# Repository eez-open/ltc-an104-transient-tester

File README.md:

LTC [AN104](http://www.linear.com/docs/29876) Closed loop load transient tester Eagle, Gebgers and BOM. It could be used for testing various LDOs, power supplies, etc.
Two PCB variants are available: 

* with power supply (ac-powered) that can be housed e.g. into Hammond diecast aluminium enclosure HM-1590U 
* without power supply (dc-powered) using two external 15 VDC sources connected with 2.1/5.5 mm DC plugs.

**Please note that max. allowed D.U.T voltage is determined with switching transistor SOA.**

**********************

Repository: www.github.com/eez-open
Web site: www.envox.hr/eez

**********************

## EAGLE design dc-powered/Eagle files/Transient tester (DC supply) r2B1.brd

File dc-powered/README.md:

LTC [AN104](http://www.linear.com/docs/29876) Closed loop load transient tester with external 2 x 15 VDC supply

**Please note that max. allowed D.U.T voltage is determined with switching transistor SOA.**

**********************

Repository: www.github.com/eez-open
Web site: www.envox.hr/eez

**********************

*EEZ 2-layer (+tKeepout +_tNames) *job script is used for generating Gerber files. Use [gerbv](http://gerbv.geda-project.org/), a free/open source Gerber viewer to inspect generated files.

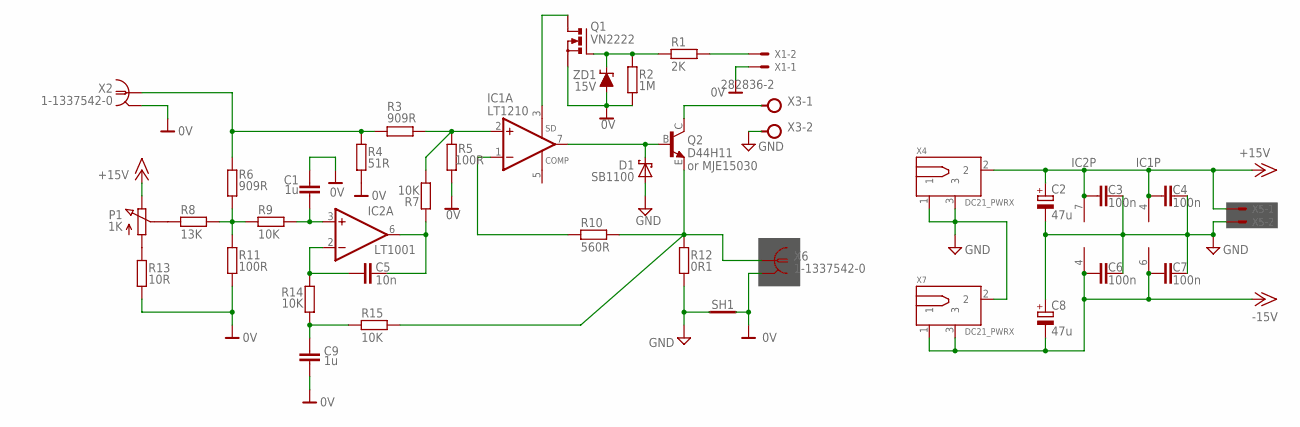
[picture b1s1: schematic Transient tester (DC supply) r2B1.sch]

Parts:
C1, C9: 1u; C050-075X075
C2, C8: 47u; ECAP2.5/7
C3, C4, C6, C7: 100n; C050-025X075
C5: 10n; C050-025X075
D1: SB1100; DO34/10
IC1: LT1210; TO220-7
IC2: LT1001; DIL08D
P1: 1K; BOURNS_POT91
Q1: VN2222; TO92-SGD
Q2: D44H11; TO220BV
R1: 2K; 0204/5
R2: 1M; 0204/5
R3, R6: 909R; 0207/10
R4: 51R; 0204/5
R5, R11: 100R; 0204/5
R7, R9, R14, R15: 10K; 0204/5
R8: 13K; 0204/5
R10: 560R; 0204/5
R12: 0R1; OAR1+2512
R13: 10R; 0204/5
SH1: SHORTH; SHORT_2
X1: 22-23-2021
X2, X6: 1-1337542-0; AMP_227161
X3: 282836-2; TBLOCK5.0_2
X4, X7: DC21_PWRX; DC-21MM
X5: 22-23-2021; MPN 22-23-2021
ZD1: 15V; DO34-ZD

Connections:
0V: C1.1, C9.2, Q1.S, R2.1, R4.1, R5.2, R11.1, R13.1, SH1.2 (GND_B), X1.1, X2.2 (GND), X6.2 (GND), ZD1.A
+15V: C2.+, C3.2, C4.2, IC1.4 (V+), IC2.7 (V+), P1.1 (E), X4.2, X5.1
-15V: C6.2, C7.2, C8.-, IC1.6 (V-), IC2.4 (V-), X7.1, X7.3
GND: C2.-, C3.1, C4.1, C6.1, C7.1, C8.+, D1.A, R12.1, R12.1.1 (1), SH1.1 (GND_A), X3.2, X4.1, X4.3, X5.2, X7.2
unnamed: IC1.1 (-IN), R10.2
unnamed: Q2.E, R10.1, R12.2, R12.2.1 (2), R15.2, X6.1
unnamed: IC1.3 (SD), Q1.D
unnamed: Q1.G, R1.2, R2.2, ZD1.C
unnamed: D1.C, IC1.7 (OUT), Q2.B
unnamed: IC1.2 (+IN), R3.2, R5.1, R7.1
unnamed: C5.1, IC2.6 (OUT), R7.2
unnamed: C5.2, IC2.2 (-IN), R14.1
unnamed: C9.1, R14.2, R15.1
unnamed: P1.2 (S), R8.2
unnamed: P1.3 (A), R13.2
unnamed: R6.1, R8.1, R9.1, R11.2
unnamed: C1.2, IC2.3 (+IN), R9.2
unnamed: R3.1, R4.2, R6.2, X2.1
unnamed: Q2.C, X3.1
unnamed: R1.1, X1.2

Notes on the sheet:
or MJE15030

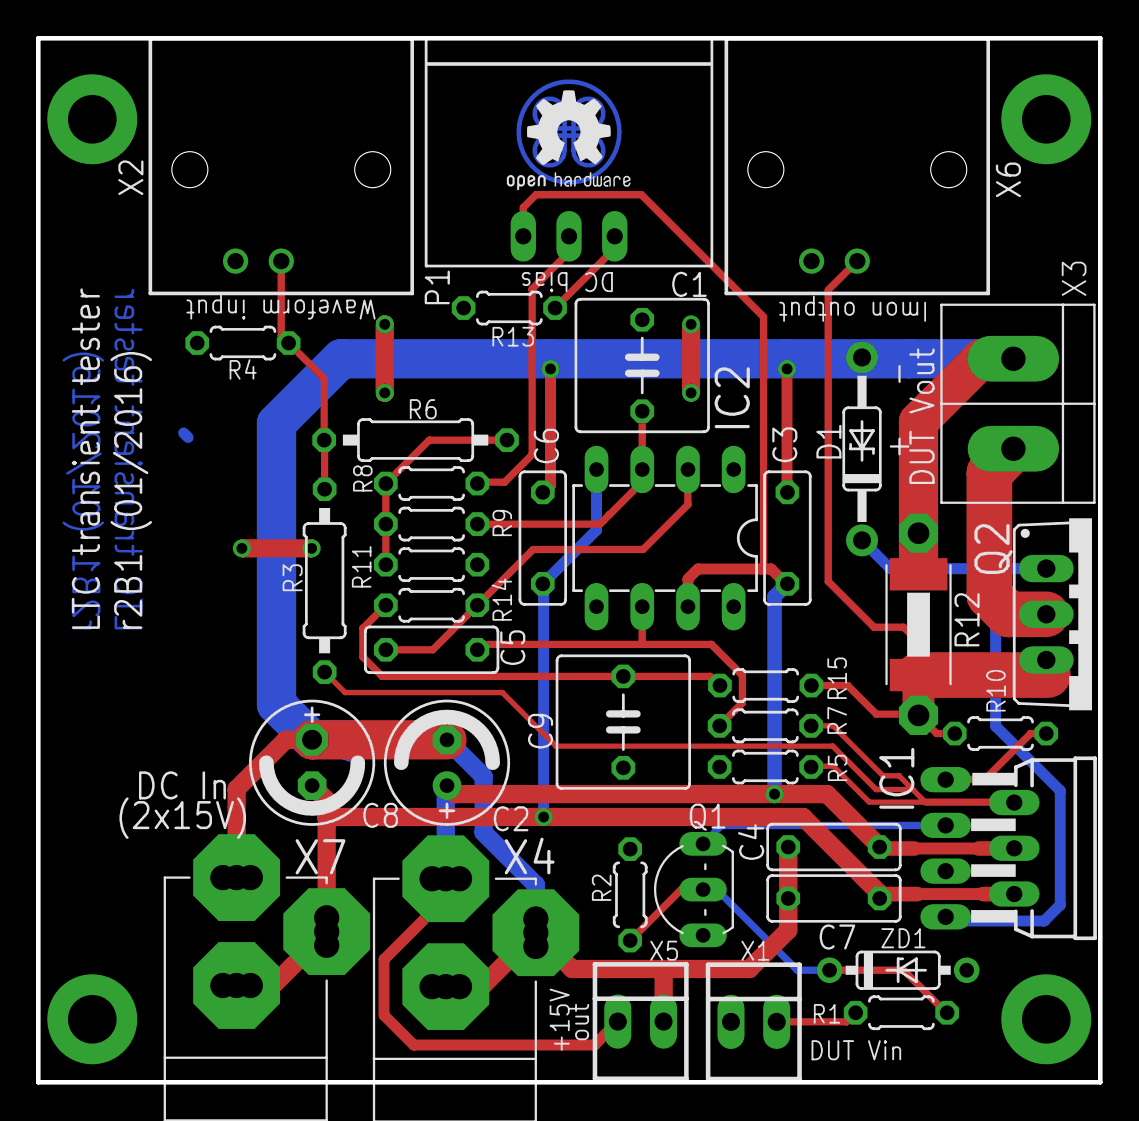
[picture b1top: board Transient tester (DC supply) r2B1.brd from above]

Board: 2 copper layers, 59.0 x 58.0 mm, 41 parts (0 on the bottom side), 20 nets.

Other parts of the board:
EEZ_SIGNATURE1: SIGNATURESMALL; SIGNATURE_5MM
GOLD_ORB_SM: OSHWLOGO_GOLD_ORB_SM; OSHW2

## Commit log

2016-01-17 enclosure name corrected
2016-01-17 picture name fixed
2021-07-16 Links updated

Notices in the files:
parts and their libraries:
EEZ_Lib1: This work is licensed under the TAPR Open Hardware License.
